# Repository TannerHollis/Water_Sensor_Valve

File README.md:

# Water Sensor Valve
 This project mimics the operation of a "Water Cop". While commercial use of this device is expensive, a simple cheap clone can be replicated for a mere dollars.
 
## Water Sensor
The water sensor is a simple wheatstone bridge with one leg of the resistor divider being the exposed metal strips in the probe. Due to variation in the installation of the product, the probe's resistivity will change. Using a wide variety of different possible probe gaps, the wheatstone bridge is configurable for up to 15 different resistor combinations. See [total_resistor_combinations.txt](https://github.com/TannerHollis/Water_Sensor_Valve/blob/main/Water_Valve_Calculations/total_resistor_combinations.txt) for all possible combinations. The purpose of this configuration is to accomodate for a wide range of possible probe resistivities.

A "dirty" or water typically found with contamination in it widely varies in it's resistivity, or it's ability to conduct electricity. Since the resistivity of air is magnitudes larger than the resistivity of water, the effect on the probes open air contacts can be ignored for the theoretical calculations. 

Contaminated water has a resitivity typically between 20 to 2000 Ohms. To calculate the theoretical resistance between two electrical wires submerged in water, one must utilize the resistance formula.

	R = p L / A
 
This device is meant to be used with a probe with a small 2mm gap and approximately 31um^2 of exposed contacts on the probe, which when submerged in conductive water yields a theoretical maximum resistance of ~127 kOhms. Tolerances must be added to assure the proper resistivity is measured. In this scenario, we would recommend using a setting of 84.777 kOhms which corresponds to jumping resistors R3 and R4 corresponding to 127 and 255 kOhm resistors. At this set point, any measured resistance below the threshold of 84.777 kOhms will trigger the closing of the valve and sounding of the alarm.

Adjustments may be needed for more sensitivity or security. For more sensitivity, refer to the resistor combination file and choose the next highest setting. For more security,  choose the next lowest setting. Continue to do so until the desired operation is achieved. 

## Custom Setting Attachment
This add-on is a customizable attachment that is configurable with either the use the included potentiometer or the solderable resistor footprint. With the included mosfet, an external controller can be attached and control the Water Sensor Valve using the connections with the use of the included external mosfet.

- [X] Test and verify first revision
- [X] Verify alarm and valve operation
- [ ] Design and print custom device housing
- [ ] Create custom setting attachment
- [ ] Control device with custom setting attachment using MCU
- [ ] Setup configurable custom setting attachement using potentiometer

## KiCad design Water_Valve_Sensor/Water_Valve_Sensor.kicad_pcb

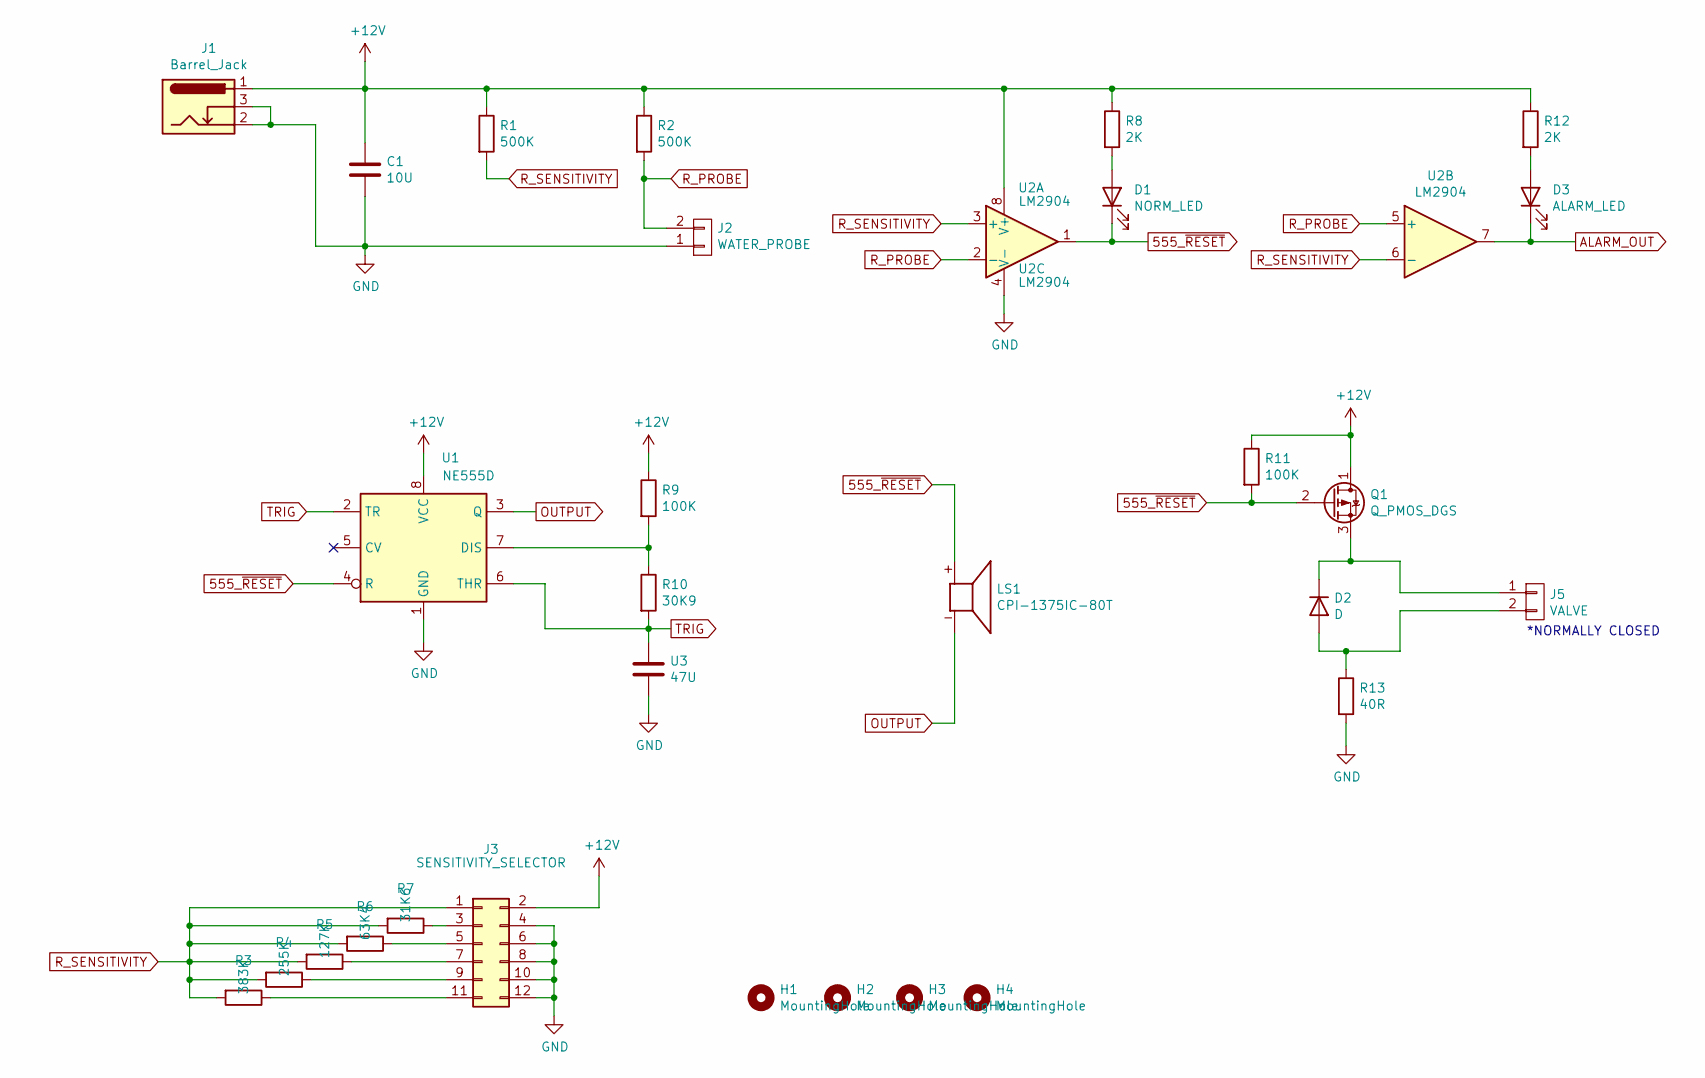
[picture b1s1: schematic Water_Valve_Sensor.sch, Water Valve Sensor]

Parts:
C1: 10U; CP_Radial_D5.0mm_P2.00mm
D1: NORM_LED; LED_D3.0mm
D2: D; D_DO-15_P10.16mm_Horizontal
D3: ALARM_LED; LED_D3.0mm
H1, H2, H3, H4: MountingHole; MountingHole_2.5mm_Pad_TopBottom
J1: Barrel_Jack; PJ-002A
J2: WATER_PROBE; PinHeader_1x02_P2.54mm_Horizontal
J3: SENSITIVITY_SELECTOR; PinHeader_2x06_P2.54mm_Vertical
J5: VALVE; PinHeader_1x02_P2.54mm_Horizontal
LS1: CPI-1375IC-80T; CUI_CPI-1375IC-80T; PARTREV 1.0
Q1: Q_PMOS_DGS; TO-92
R1, R2: 500K; R_Axial_DIN0207_L6.3mm_D2.5mm_P7.62mm_Horizontal
R3: 383K; R_Axial_DIN0207_L6.3mm_D2.5mm_P7.62mm_Horizontal
R4: 255K; R_Axial_DIN0207_L6.3mm_D2.5mm_P7.62mm_Horizontal
R5: 127K; R_Axial_DIN0207_L6.3mm_D2.5mm_P7.62mm_Horizontal
R6: 63K4; R_Axial_DIN0207_L6.3mm_D2.5mm_P7.62mm_Horizontal
R7: 31K6; R_Axial_DIN0207_L6.3mm_D2.5mm_P7.62mm_Horizontal
R8, R12: 2K; R_Axial_DIN0207_L6.3mm_D2.5mm_P7.62mm_Horizontal
R9, R11: 100K; R_Axial_DIN0207_L6.3mm_D2.5mm_P7.62mm_Horizontal
R10: 30K9; R_Axial_DIN0207_L6.3mm_D2.5mm_P7.62mm_Horizontal
R13: 40R; R_Axial_DIN0207_L6.3mm_D2.5mm_P7.62mm_Horizontal
U1: NE555D; SOIC-8_3.9x4.9mm_P1.27mm
U2: LM2904; SOIC-8_3.9x4.9mm_P1.27mm
U3: 47U; CP_Radial_D5.0mm_P2.00mm

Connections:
555_~RESET~: D1.1 (K), LS1.P, Q1.2 (G), R11.2, U1.4 (R), U2.1
+12V: C1.1, J1.1, J3.2, Q1.1 (D), R1.1, R2.1, R8.1, R9.1, R11.1, R12.1, U1.8 (VCC), U2.8 (V+)
ALARM_OUT: D3.1 (K), U2.7
GND: C1.2, J1.2, J1.3, J2.1, J3.4, J3.6, J3.8, J3.10, J3.12, R13.2, U1.1 (GND), U2.4 (V-), U3.2
unnamed: D1.2 (A), R8.2
unnamed: D2.1 (K), J5.1, Q1.3 (S)
unnamed: D2.2 (A), J5.2, R13.1
unnamed: D3.2 (A), R12.2
unnamed: J3.3, R7.1
unnamed: J3.5, R6.1
unnamed: J3.7, R5.1
unnamed: J3.9, R4.1
unnamed: J3.11, R3.1
unnamed: R9.2, R10.1, U1.7 (DIS)
OUTPUT: LS1.N, U1.3 (Q)
R_PROBE: J2.2, R2.2, U2.2 (-), U2.5 (+)
R_SENSITIVITY: J3.1, R1.2, R3.2, R4.2, R5.2, R6.2, R7.2, U2.3 (+), U2.6 (-)
TRIG: R10.2, U1.2 (TR), U1.6 (THR), U3.1

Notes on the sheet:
*NORMALLY CLOSED

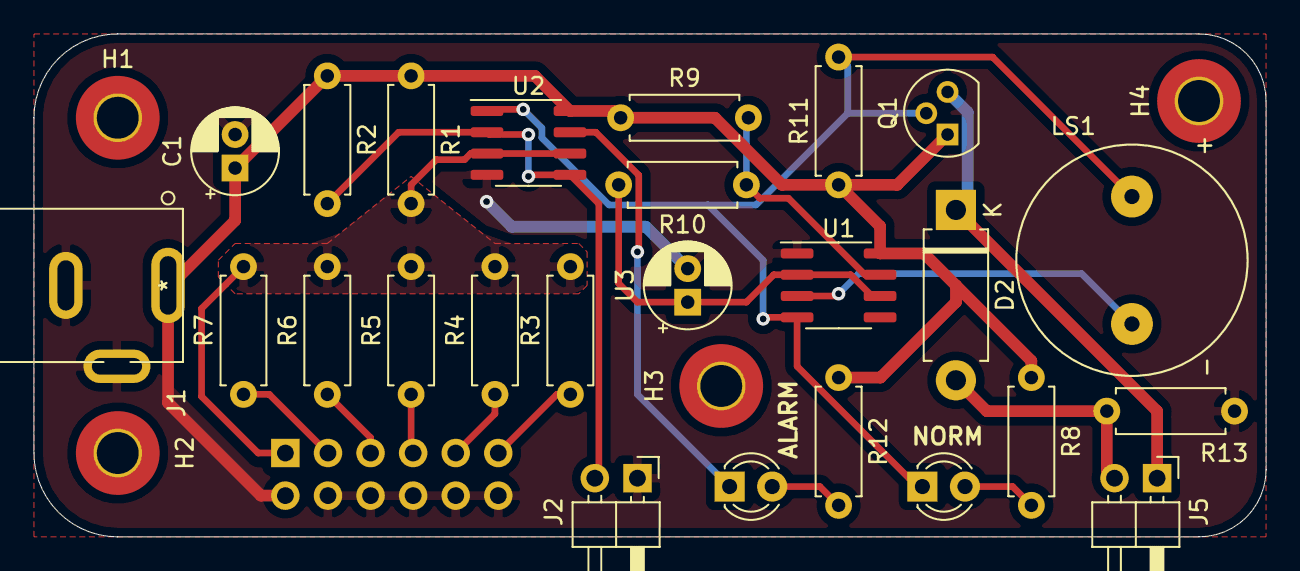
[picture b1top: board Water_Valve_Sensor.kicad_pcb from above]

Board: 2 copper layers, 73.5 x 30.0 mm, 30 parts (1 on the bottom side), 18 nets.

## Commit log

2021-08-27 Removed Files
    Removed Files
2021-08-27 Deleted Files
    Deleted Files
2021-08-30 Fixed Wiring Issue
    Added support for 2x6 header for Custom Setting Attachment
2021-08-31 Updated Resistor Combination
    Updated Resistor Combination
2021-09-02 Changes to resistor selections
    Updated sensitivty resistors.
2021-09-02 Instruction_Manual
    Updated the Instruction Manual

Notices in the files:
parts and their libraries:
Copyright 2021 Accelerated Designs. All rights reserved.
